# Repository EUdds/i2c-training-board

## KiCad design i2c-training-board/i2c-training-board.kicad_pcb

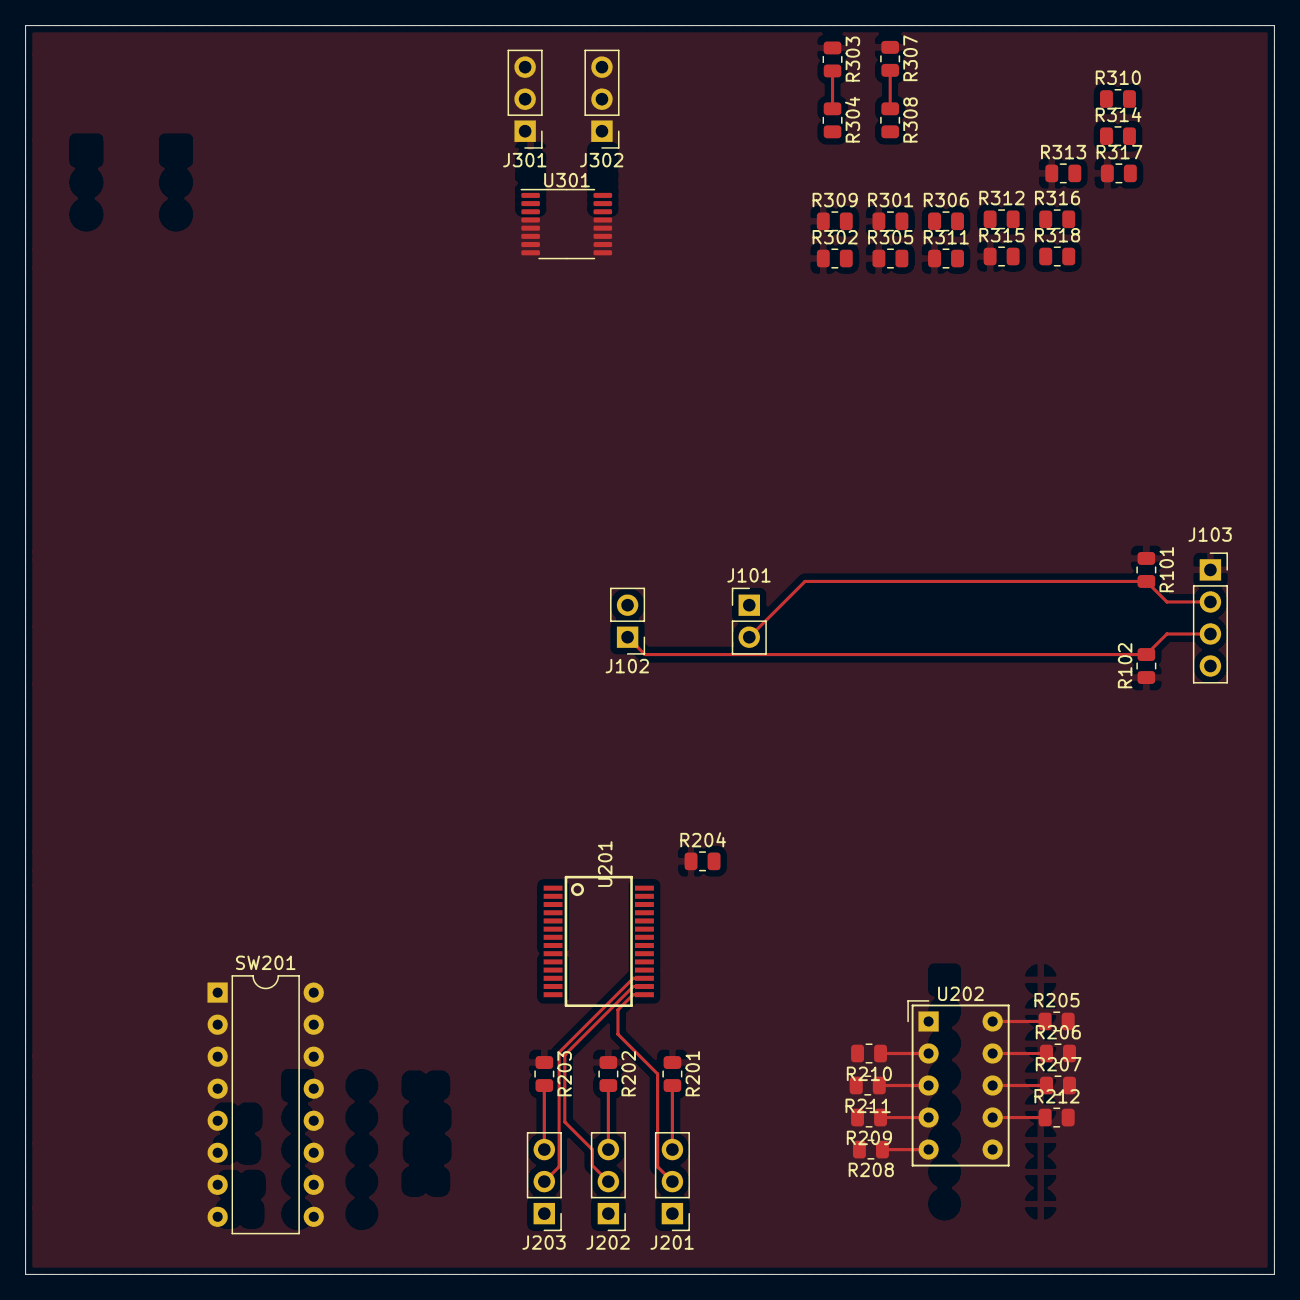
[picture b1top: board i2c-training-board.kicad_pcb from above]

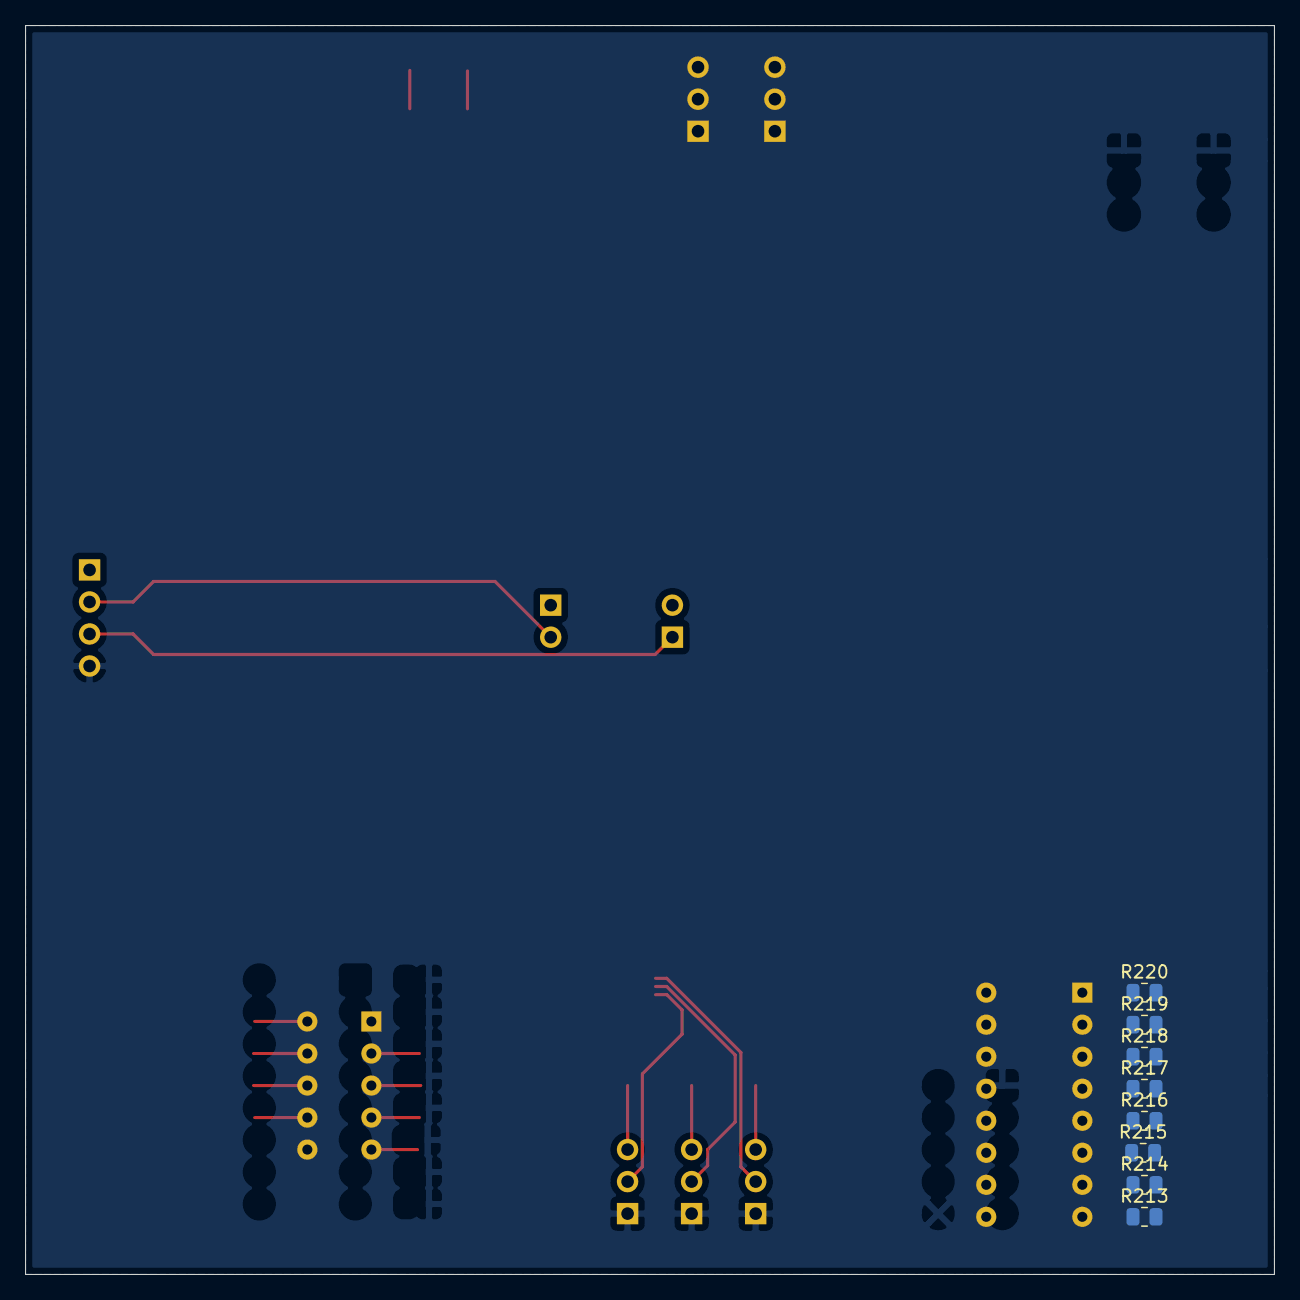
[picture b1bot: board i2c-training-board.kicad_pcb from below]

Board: 2 copper layers, 99.1 x 99.1 mm, 52 parts (8 on the bottom side), 49 nets.

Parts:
J101, J102: Conn_01x02; PinHeader_1x02_P2.54mm_Vertical
J103: Conn_01x04; PinSocket_1x04_P2.54mm_Vertical
J201, J202, J203, J301, J302: Conn_01x03; PinHeader_1x03_P2.54mm_Vertical
R101, R102, R201, R202, R203, R204, R301, R302: 4.7K; R_0805_2012Metric
R205, R206, R207, R208, R209, R210, R211, R212: 220; R_0805_2012Metric
R213, R214, R215, R216, R217, R218, R219: 10k; R_0805_2012Metric
R220: 10K; R_0805_2012Metric
R303: 100; R_0805_2012Metric
R304, R306, R308, R310, R312, R314, R316, R318: 1K; R_0805_2012Metric
R305: 510; R_0805_2012Metric
R307: 200; R_0805_2012Metric
R309: 620; R_0805_2012Metric
R311: 300; R_0805_2012Metric
R313: 750; R_0805_2012Metric
R315: 470; R_0805_2012Metric
R317: 820; R_0805_2012Metric
SW201: SW_DIP_x08; DIP-16_W7.62mm
U201: MCP23017_SS; SSOP28
U202: HDSP-7401
U301: ADC128D818; TSSOP-16_4.4x5mm_P0.65mm

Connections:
+3V3: J103.1, R101.1, R102.1, R201.1, R202.1, R203.1, R204.1, R301.1, R302.1, R303.1, R305.1, R307.1, R309.1, R311.1, R313.1, R315.1, R317.1, SW201.9, SW201.10, SW201.11, SW201.12, SW201.13, SW201.14, SW201.15, SW201.16, U201.9, U301.1, U301.5
/ADC/ADC_A0: J301.2, U301.7
/ADC/ADC_A1: J302.2, U301.8
/ADC/ADC_SCL: J102.2, U301.3
/ADC/ADC_SDA: J101.1, U301.2
/ADC/VDIV3: R315.2, R316.1
/ADC/VDIV_0: R303.2, R304.1, U301.16
/ADC/VDIV_1: R307.2, R308.1, U301.15
/ADC/VDIV_2: R311.2, R312.1, U301.14
/ADC/VDIV_4: R305.2, R306.1, U301.12
/ADC/VDIV_5: R309.2, R310.1, U301.11
/ADC/VDIV_6: R313.2, R314.1, U301.10
/ADC/VDIV_7: R317.2, R318.1, U301.9
/IOX/IOX_A0: J201.2, U201.15
/IOX/IOX_A1: J202.2, U201.16
/IOX/IOX_A2: J203.2, U201.17
/IOX/IOX_SCK: J102.1, J103.3, R102.2, U201.12
/IOX/IOX_SDA: J101.2, J103.2, R101.2, U201.13
GND: J103.4, J201.1, J202.1, J203.1, J301.1, J302.1, R213.2, R214.2, R215.2, R216.2, R217.2, R218.2, R219.2, R220.2, R304.2, R306.2, R308.2, R310.2, R312.2, R314.2, R316.2, R318.2, U201.10, U202.1, U202.6, U301.4
unnamed: J201.3, R201.2
unnamed: J202.3, R202.2
unnamed: J203.3, R203.2
unnamed: J301.3, R301.2
unnamed: J302.3, R302.2
unnamed: R204.2, U201.18
unnamed: R205.1, U202.10
unnamed: R205.2, U201.21
unnamed: R206.1, U202.9
unnamed: R206.2, U201.22
unnamed: R207.1, U202.8
unnamed: R207.2, U201.23
unnamed: R208.1, U202.5
unnamed: R208.2, U201.24
unnamed: R209.1, U202.4
unnamed: R209.2, U201.25
unnamed: R210.1, U202.2
unnamed: R210.2, U201.26
unnamed: R211.1, U202.3
unnamed: R211.2, U201.27
unnamed: R212.1, U202.7
unnamed: R212.2, U201.28
unnamed: R213.1, SW201.8, U201.8
unnamed: R214.1, SW201.7, U201.7
unnamed: R215.1, SW201.6, U201.6
unnamed: R216.1, SW201.5, U201.5
unnamed: R217.1, SW201.4, U201.4
unnamed: R218.1, SW201.3, U201.3
unnamed: R219.1, SW201.2, U201.2
unnamed: R220.1, SW201.1, U201.1
